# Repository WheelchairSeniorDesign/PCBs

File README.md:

# PCB Design in Git

- We will be using git to store KiCad files as well so that we can have a running record of them.
- Put all the PCBs in a subfolder in the PCB repo.
- Make a branch for your board, and only work on that board on the corresponding branch.
- Don’t delete your branch once you merge it; keep making changes on that branch.
- Only one person should work on a board at a time, and all changes should be committed before the next person works on it.

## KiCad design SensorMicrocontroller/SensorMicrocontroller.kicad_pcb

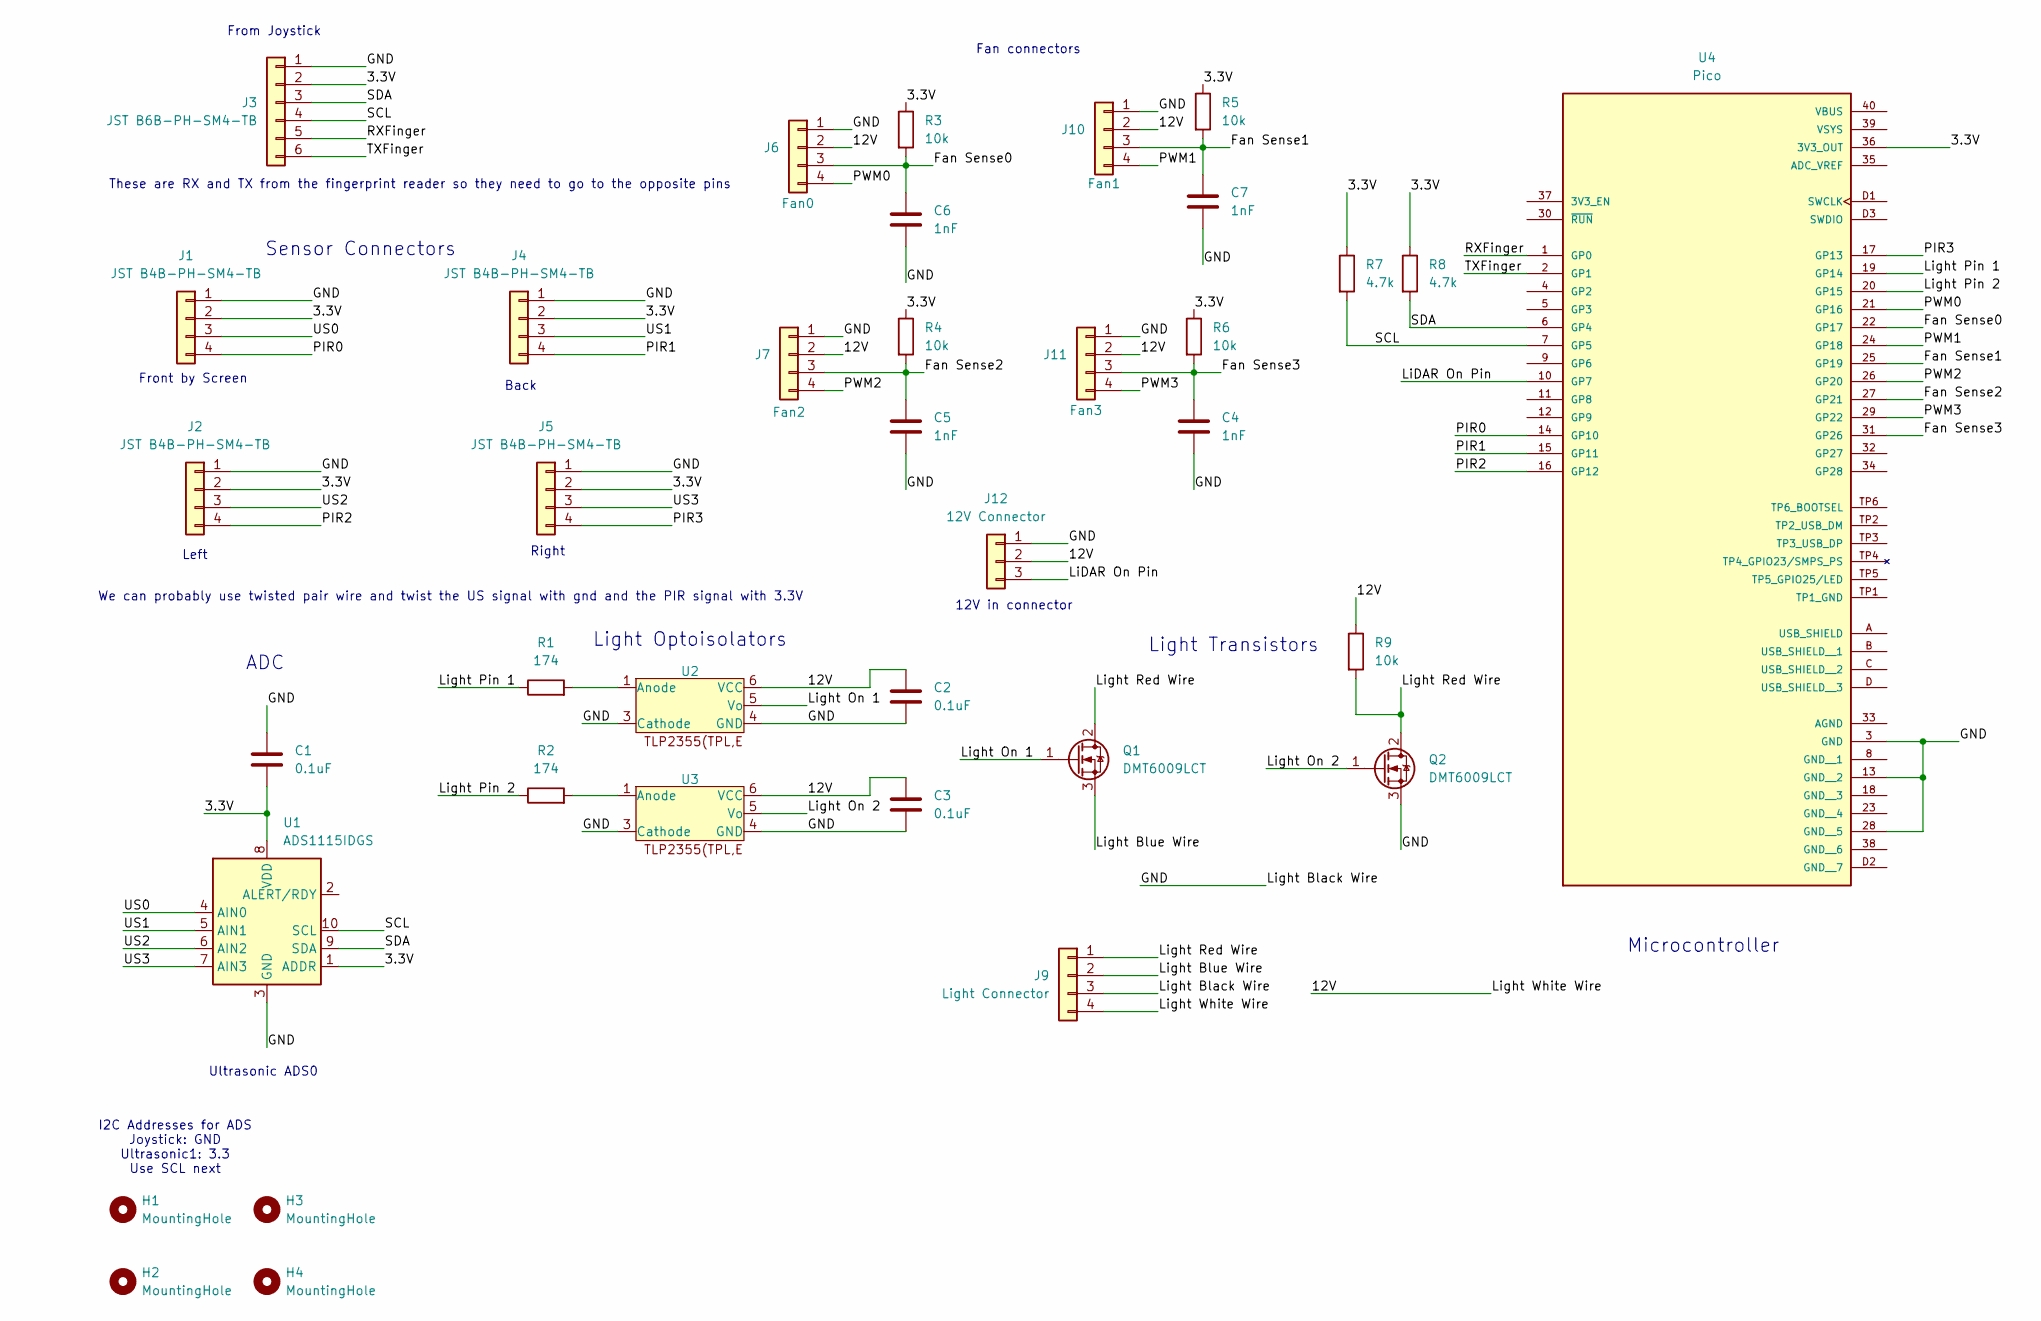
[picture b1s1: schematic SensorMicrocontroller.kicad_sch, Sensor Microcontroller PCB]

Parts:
C1, C2, C3: 0.1uF; C_0805_2012Metric; Manufacturer Part Number CC0805KRX7R9BB104
C4, C5, C6, C7: 1nF; C_0805_2012Metric; Manufacturer Part Number C0805C102K4RACTU
H1, H2, H3, H4: MountingHole; MountingHole_3.2mm_M3_ISO7380_Pad
J1, J2, J4, J5: JST B4B-PH-SM4-TB; JST_PH_B4B-PH-SM4-TB_1x04-1MP_P2.00mm_Vertical; Manufacturer Part Number B4B-PH-SM4-TB
J3: JST B6B-PH-SM4-TB; JST_PH_B6B-PH-SM4-TB_1x06-1MP_P2.00mm_Vertical; Manufacturer Part Number B6B-PH-SM4-TB
J6, J7, J10, J11: FanPinHeader_1x04_P2.54mm_Vertical; Manufacturer Part Number 0470531000
J9: Light Connector; JST_EH_B4B-EH-A_1x04_P2.50mm_Vertical; Manufacturer Part Number B4B-EH-A
J12: 12V Connector; JST_PH_B3B-PH-SM4-TB_1x03-1MP_P2.00mm_Vertical; Manufacturer Part Number B3B-PH-SM4-TB
Q1, Q2: DMT6009LCT; TO-220-3_Vertical; Manufacturer Part Number DMT6009LCT
R1, R2: 174; R_0805_2012Metric; Manufacturer Part Number RC0805FR-07174RL
R3, R4, R5, R6, R9: 10k; R_0805_2012Metric; Manufacturer Part Number RR1220P-103-D
R7, R8: 4.7k; R_0805_2012Metric; Manufacturer Part Number CRCW08054K70FKEAC
U1: ADS1115IDGS; VSSOP-10_3x3mm_P0.5mm; Manufacturer Part Number ADS1115IDGSR
U2, U3: Optoisolators; SO-5-6_4.55x3.7mm_P1.27mm; Manufacturer Part Number TLP2355(TPL,E
U4: Pico; pico; PARTREV 1.9

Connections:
/3.3V: C1.2, J1.2, J2.2, J3.2, J4.2, J5.2, R3.1, R4.1, R5.1, R6.1, R7.1, R8.1, U1.1 (ADDR), U1.8 (VDD), U4.36 (3V3_OUT)
/12V: C2.1, C3.1, J6.2, J7.2, J9.4, J10.2, J11.2, J12.2, R9.1, U2.6 (VCC), U3.6 (VCC)
/Fan Sense0: C6.1, J6.3, R3.2, U4.22 (GP17)
/Fan Sense1: C7.1, J10.3, R5.2, U4.25 (GP19)
/Fan Sense2: C5.1, J7.3, R4.2, U4.27 (GP21)
/Fan Sense3: C4.1, J11.3, R6.2, U4.31 (GP26)
/GND: C1.1, C2.2, C3.2, C4.2, C5.2, C6.2, C7.2, J1.1, J2.1, J3.1, J4.1, J5.1, J6.1, J7.1, J9.3, J10.1, J11.1, J12.1, Q2.3 (S), U1.3 (GND), U2.3 (Cathode), U2.4 (GND), U3.3 (Cathode), U3.4 (GND), U4.3 (GND), U4.13 (GND__2), U4.28 (GND__5)
/LiDAR On Pin: J12.3, U4.10 (GP7)
/Light Blue Wire: J9.2, Q1.3 (S)
/Light On 1: Q1.1 (G), U2.5 (Vo)
/Light On 2: Q2.1 (G), U3.5 (Vo)
/Light Pin 1: R1.1, U4.19 (GP14)
/Light Pin 2: R2.1, U4.20 (GP15)
/Light Red Wire: J9.1, Q1.2 (D), Q2.2 (D), R9.2
/PIR0: J1.4, U4.14 (GP10)
/PIR1: J4.4, U4.15 (GP11)
/PIR2: J2.4, U4.16 (GP12)
/PIR3: J5.4, U4.17 (GP13)
/PWM0: J6.4, U4.21 (GP16)
/PWM1: J10.4, U4.24 (GP18)
/PWM2: J7.4, U4.26 (GP20)
/PWM3: J11.4, U4.29 (GP22)
/RXFinger: J3.5, U4.1 (GP0)
/SCL: J3.4, R7.2, U1.10 (SCL), U4.7 (GP5)
/SDA: J3.3, R8.2, U1.9 (SDA), U4.6 (GP4)
/TXFinger: J3.6, U4.2 (GP1)
/US0: J1.3, U1.4 (AIN0)
/US1: J4.3, U1.5 (AIN1)
/US2: J2.3, U1.6 (AIN2)
/US3: J5.3, U1.7 (AIN3)
unnamed: R1.2, U2.1 (Anode)
unnamed: R2.2, U3.1 (Anode)

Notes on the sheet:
Microcontroller
Right
ADC
Light Transistors
Back
Sensor Connectors
Left
These are RX and TX from the fingerprint reader so they need to go to the opposite pins
From Joystick
Front by Screen
Fan connectors
Light Optoisolators
Ultrasonic ADS0
I2C Addresses for ADS Joystick: GND Ultrasonic1: 3.3 Use SCL next
12V in connector
We can probably use twisted pair wire and twist the US signal with gnd and the PIR signal with 3.3V

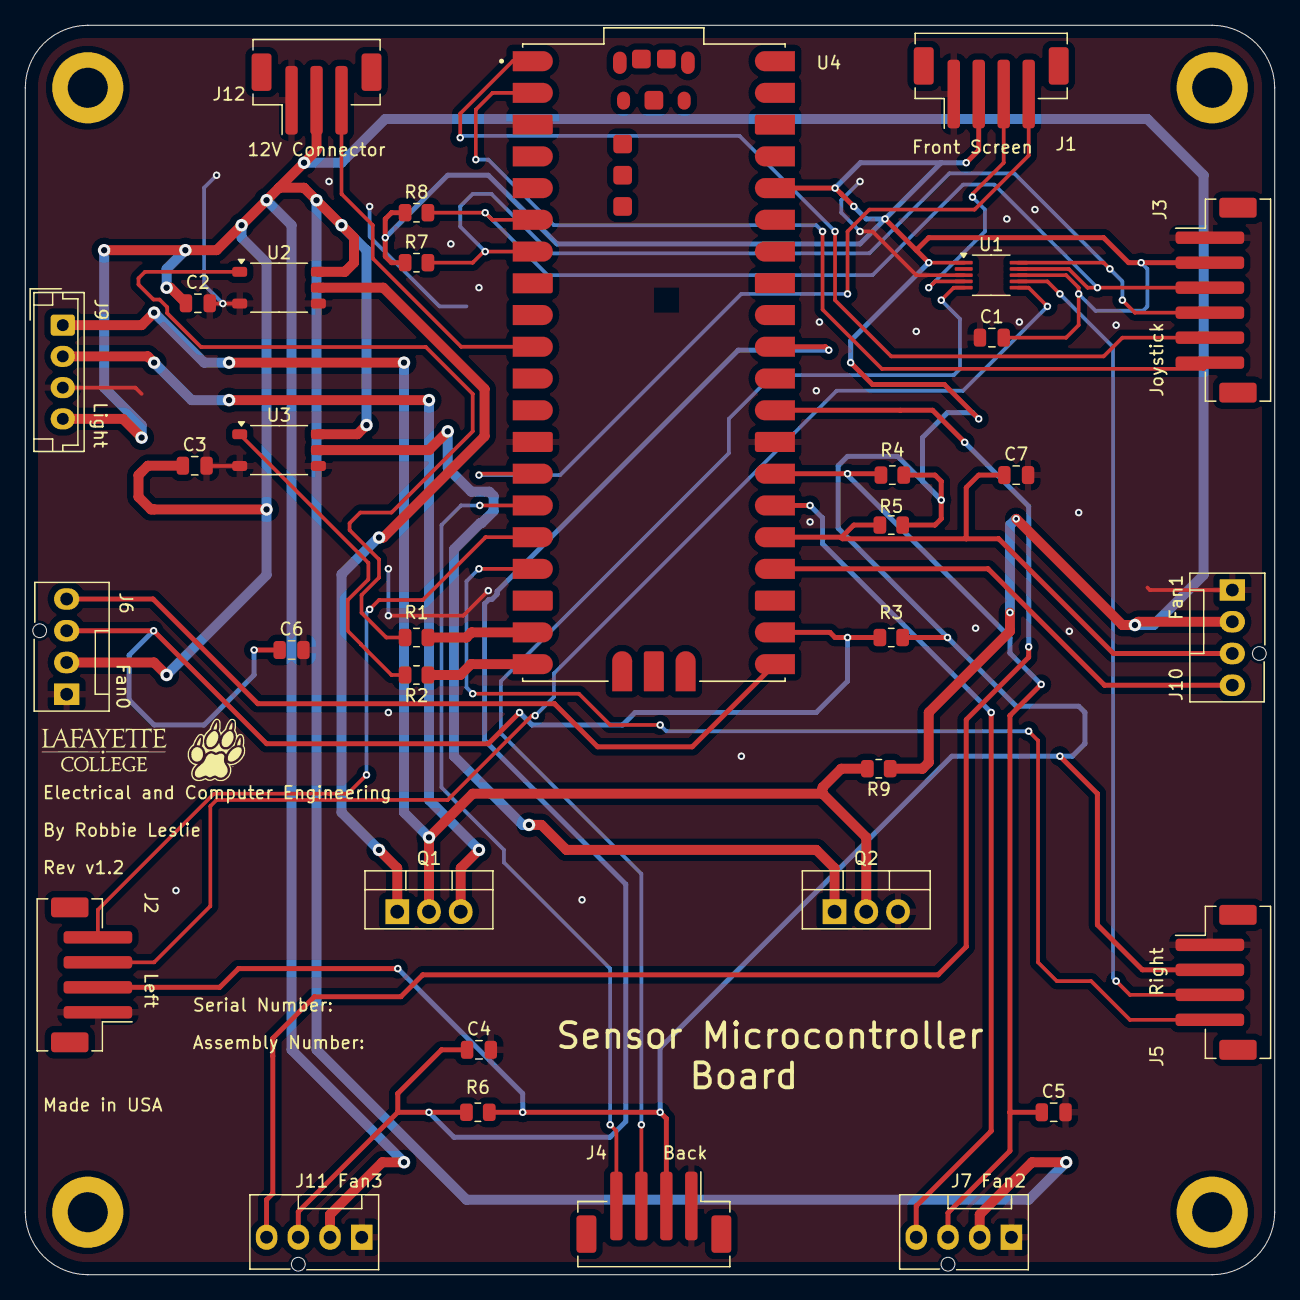
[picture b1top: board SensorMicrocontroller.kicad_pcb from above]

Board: 2 copper layers, 100.0 x 100.0 mm, 37 parts (0 on the bottom side), 32 nets.

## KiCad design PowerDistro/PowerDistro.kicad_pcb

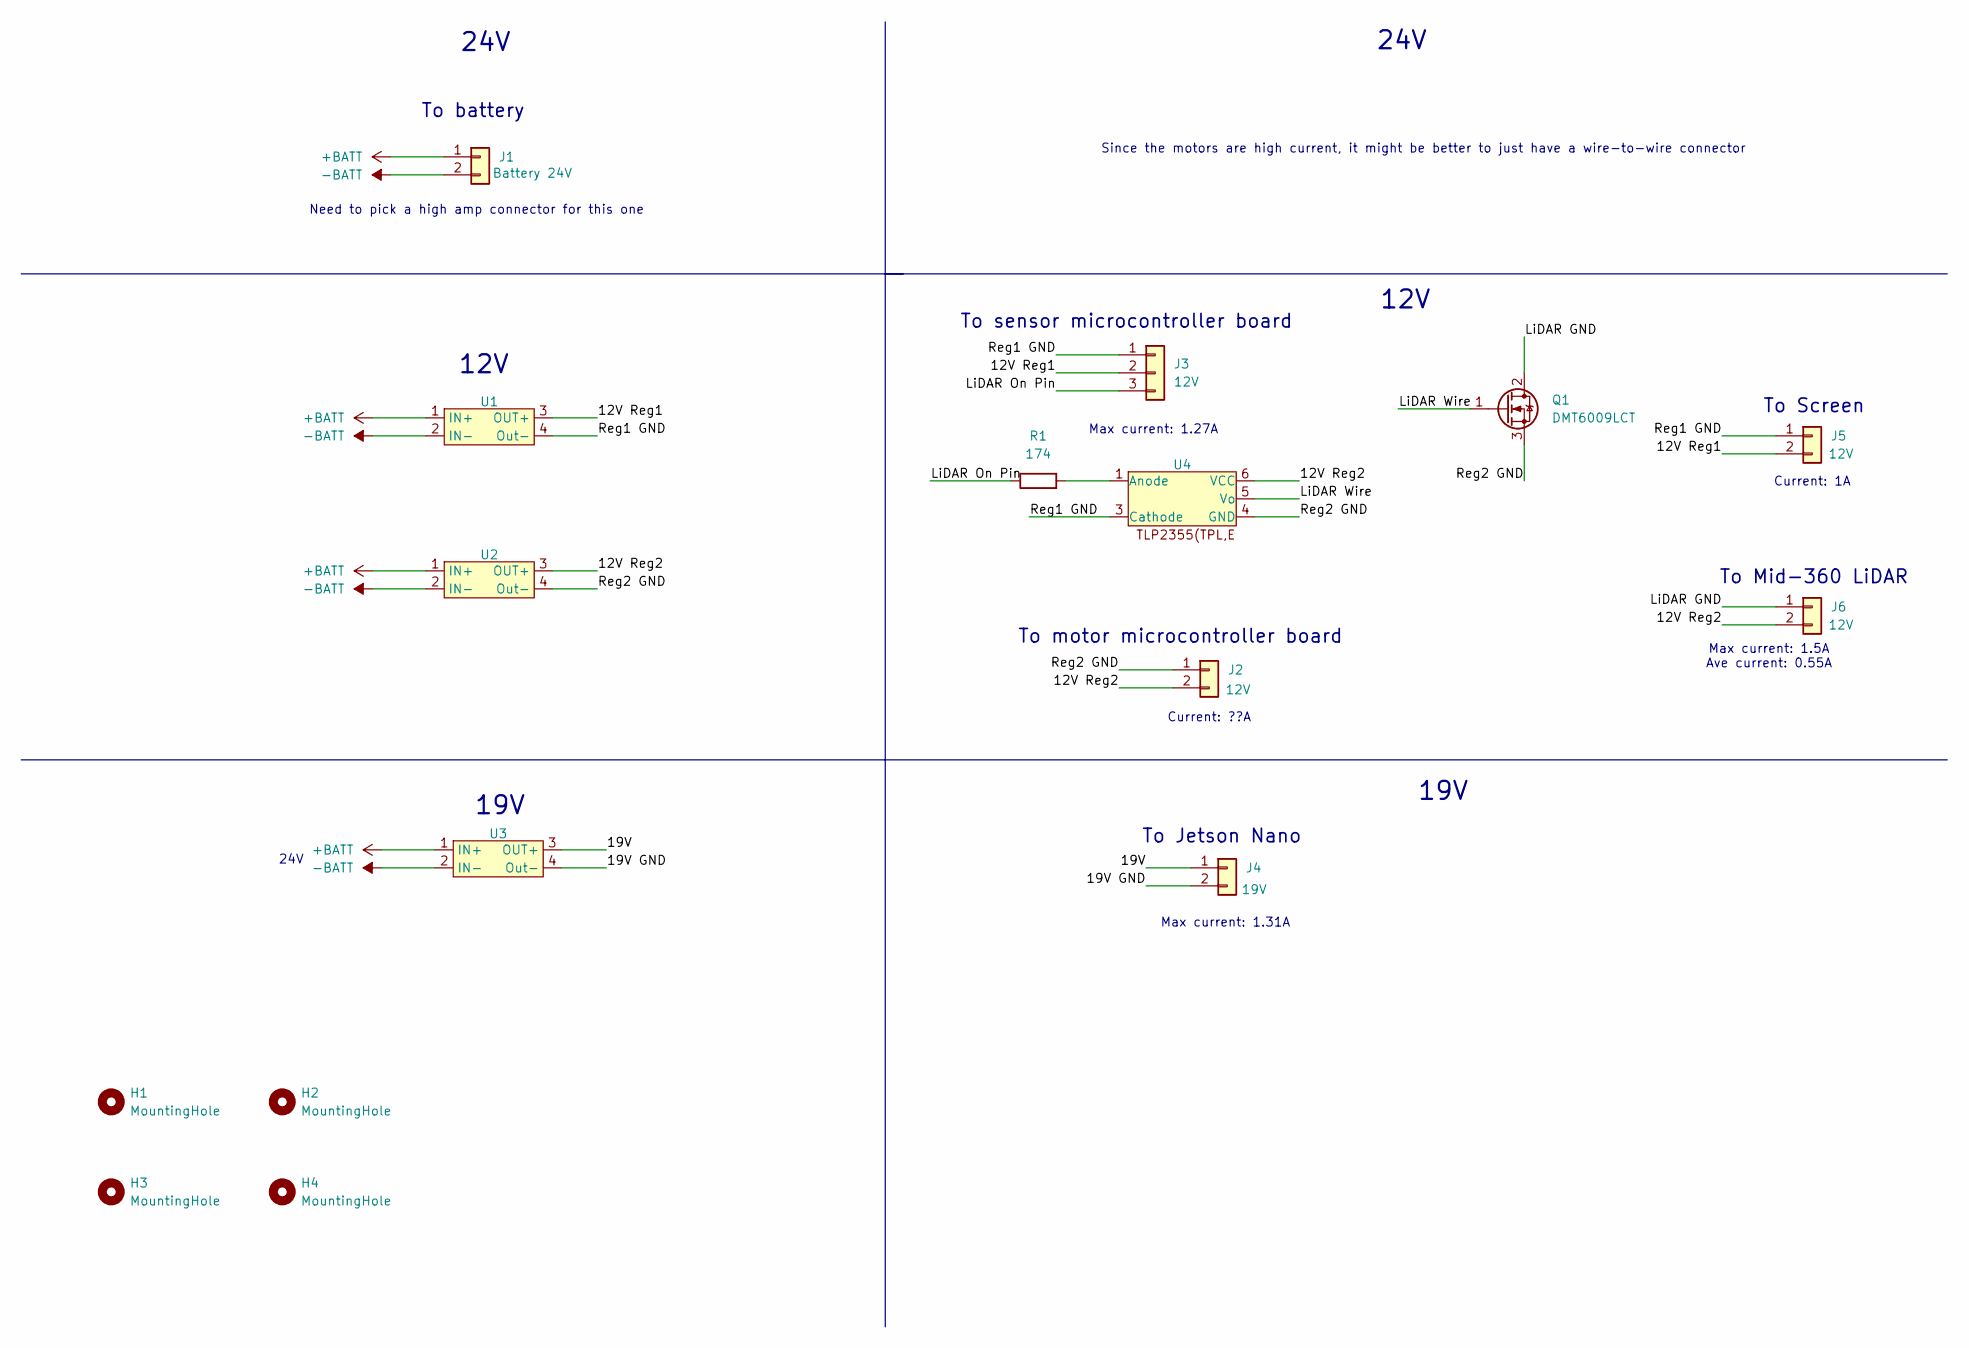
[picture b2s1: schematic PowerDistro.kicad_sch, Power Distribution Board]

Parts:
H1, H2, H3, H4: MountingHole; MountingHole_3.2mm_M3_ISO7380_Pad
J1: Molex_Mini-Fit_Jr_5566-02A_2x01_P4.20mm_Vertical; Manufacturer Part Number 0039290023
J2: JST_PH_S2B-PH-SM4-TB_1x02-1MP_P2.00mm_Horizontal; Manufacturer Part Number S2B-PH-SM4-TB
J3: 12V; JST_PH_S3B-PH-SM4-TB_1x03-1MP_P2.00mm_Horizontal; Manufacturer Part Number S3B-PH-SM4-TB
J4, J5, J6: JST_XH_S2B-XH-A-1_1x02_P2.50mm_Horizontal; Manufacturer Part Number S2B-XH-A-1
Q1: DMT6009LCT; TO-220-3_Vertical; Manufacturer Part Number DMT6009LCT
R1: 174; R_0805_2012Metric; Manufacturer Part Number RC0805FR-07174RL
U1, U2, U3: LM2596
U4: Optoisolators; SO-5-6_4.55x3.7mm_P1.27mm; Manufacturer Part Number TLP2355(TPL,E

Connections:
+BATT: J1.1, U1.1 (IN+), U2.1 (IN+), U3.1 (IN+)
-BATT: J1.2, U1.2 (IN-), U2.2 (IN-), U3.2 (IN-)
/12V Reg1: J3.2, J5.2, U1.3 (OUT+)
/12V Reg2: J2.2, J6.2, U2.3 (OUT+), U4.6 (VCC)
/19V: J4.1, U3.3 (OUT+)
/19V GND: J4.2, U3.4 (Out-)
/LiDAR GND: J6.1, Q1.2 (D)
/LiDAR On Pin: J3.3, R1.1
/LiDAR Wire: Q1.1 (G), U4.5 (Vo)
/Reg1 GND: J3.1, J5.1, U1.4 (Out-), U4.3 (Cathode)
/Reg2 GND: J2.1, Q1.3 (S), U2.4 (Out-), U4.4 (GND)
unnamed: R1.2, U4.1 (Anode)

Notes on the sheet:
Current: 1A
24V
To Jetson Nano
To battery
19V
12V
Max current: 1.27A
Since the motors are high current, it might be better to just have a wire-to-wire connector
To sensor microcontroller board
To motor microcontroller board
To Mid-360 LiDAR
Need to pick a high amp connector for this one
To Screen
Current: ??A
Max current: 1.5A Ave current: 0.55A
Max current: 1.31A

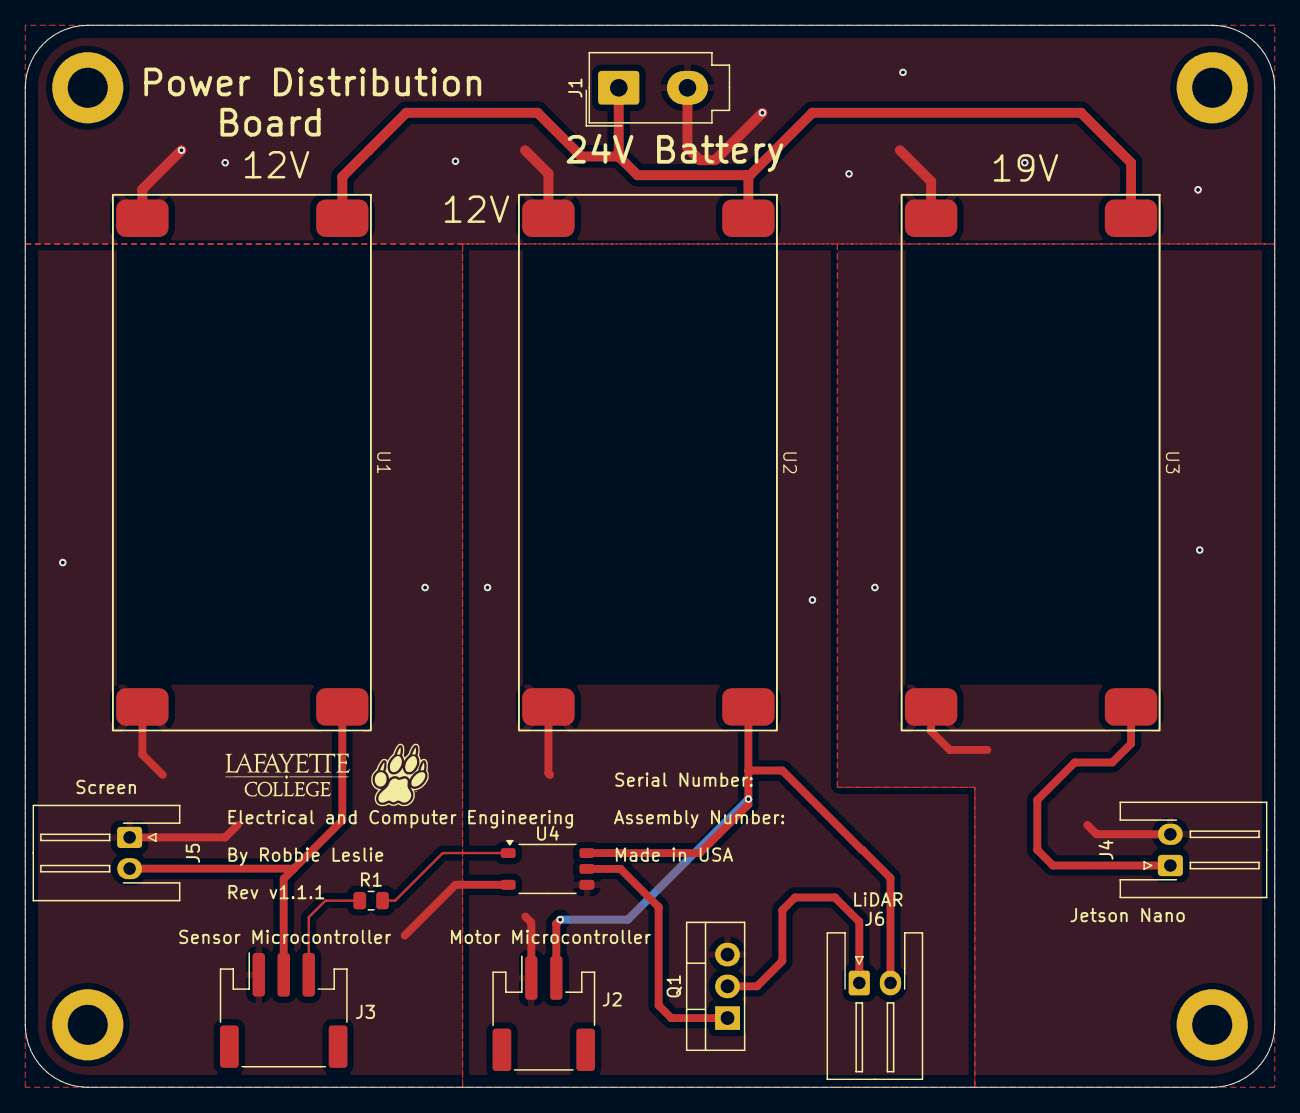
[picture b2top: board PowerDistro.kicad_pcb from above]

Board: 2 copper layers, 100.0 x 85.0 mm, 16 parts (0 on the bottom side), 12 nets.

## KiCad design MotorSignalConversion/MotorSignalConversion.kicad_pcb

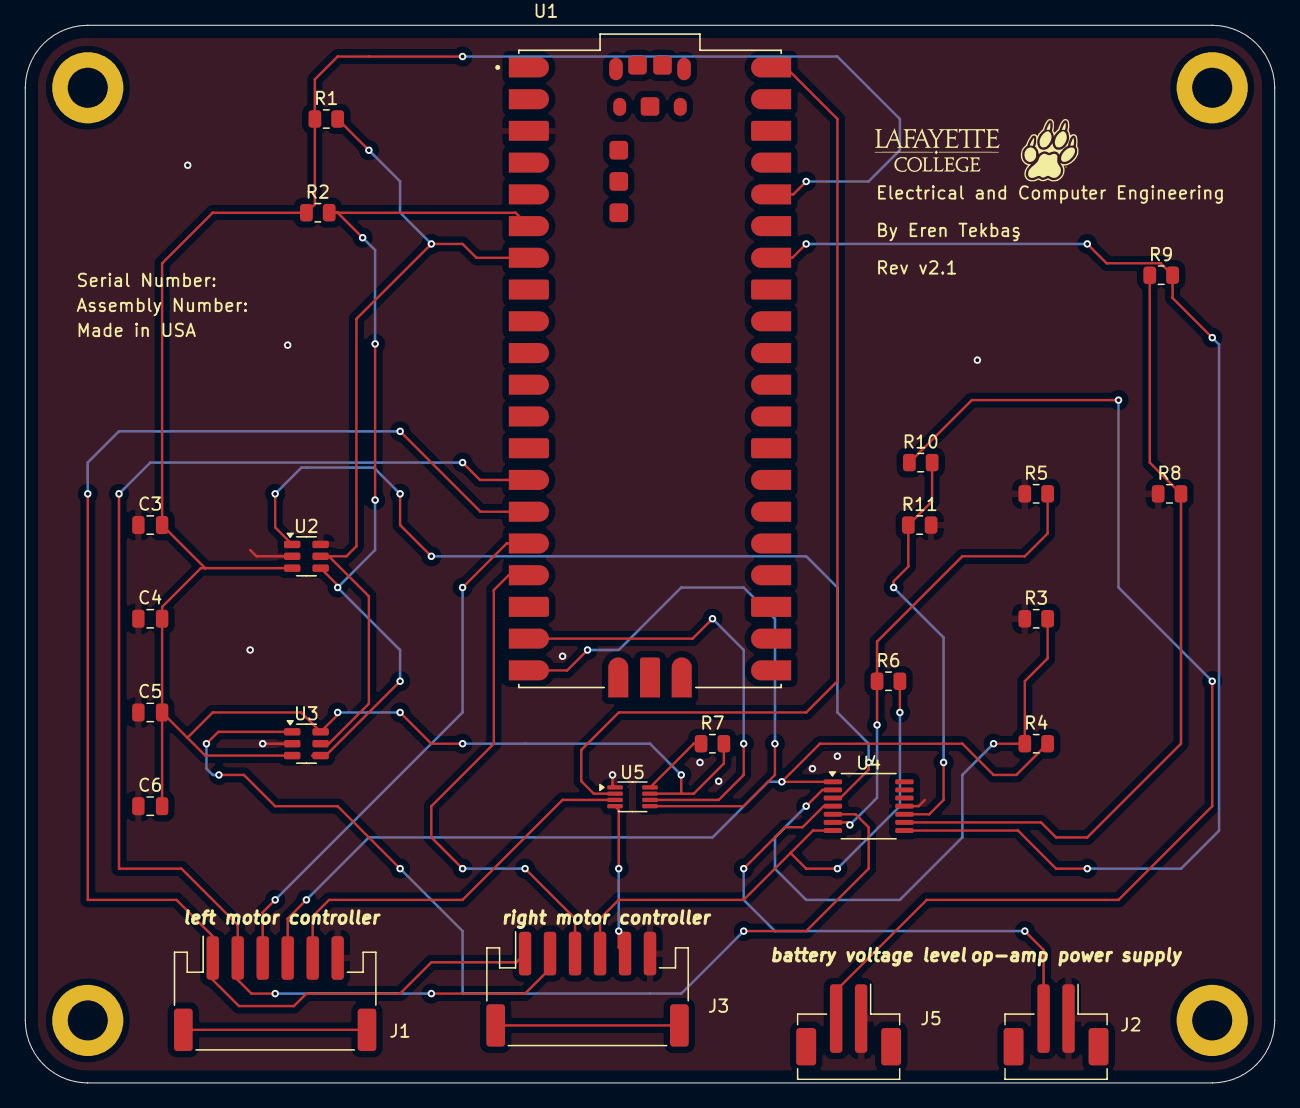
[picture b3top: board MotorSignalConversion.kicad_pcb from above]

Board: 2 copper layers, 100.0 x 84.7 mm, 28 parts (0 on the bottom side), 25 nets.

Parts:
C3, C5: 10 uF; C_0805_2012Metric
C4, C6: 0.1 uF; C_0805_2012Metric
H1, H2, H3, H4: MountingHole; MountingHole_3.2mm_M3_ISO7380_Pad
J1, J3: Conn_01x06_MountingPin; JST_PH_S6B-PH-SM4-TB_1x06-1MP_P2.00mm_Horizontal
J2, J5: Conn_01x02; JST_PH_B2B-PH-SM4-TB_1x02-1MP_P2.00mm_Vertical
R1, R2: 4.7K; R_0805_2012Metric
R3, R5: 900; R_0805_2012Metric
R4, R6: 2.1K; R_0805_2012Metric
R7: 200K; R_0805_2012Metric
R8, R11: 10K; R_0805_2012Metric
R9: 91K; R_0805_2012Metric
R10: 820K; R_0805_2012Metric
U1: SC0915; pico
U2, U3: MCP4725xxx-xCH; SOT-23-6
U4: LM324; TSSOP-14_4.4x5mm_P0.65mm
U5: LSF0102DCUR; VSSOP-8_2.3x2mm_P0.5mm

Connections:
/3V3_OUT: C3.2, C4.2, C5.2, C6.2, R1.1, R2.1, R7.2, U1.36 (3V3_OUT), U2.3 (VDD), U3.3 (VDD), U3.6 (A0), U5.7 (VREF_B)
/5V_OUT: U1.40 (VBUS), U5.2 (VREF_A)
/12V: J2.2, U4.4 (V+)
/BatteryLevelRegulated: R9.2, U1.34 (GP28), U4.8
/BatteryLevelUnregulated: J5.2, R10.1
/Brake: J1.2, J3.2, U1.14 (GP10)
/DirectionL: J1.3, U1.16 (GP12)
/DirectionR: J3.3, U1.17 (GP13)
/Enable: J1.1, J3.1, U1.15 (GP11)
/GND: C3.1, C4.1, C5.1, C6.1, J1.6, J2.1, J3.6, J5.1, R3.1, R5.1, R8.1, R11.2, U1.3 (GND), U2.2 (VSS), U2.6 (A0), U3.2 (VSS), U4.11 (V-), U5.1 (GND)
/I2C SCL: R1.2, U1.7 (GP5), U2.5 (SCL), U3.5 (SCL)
/I2C SDA: R2.2, U1.6 (GP4), U2.4 (SDA), U3.4 (SDA)
/SpeedLeft: J1.4, R4.2, U4.1
/SpeedReadRegulatedL: U1.19 (GP14), U5.6 (B1)
/SpeedReadRegulatedR: U1.20 (GP15), U5.5 (B2)
/SpeedReadUL: J1.5, U5.3 (A1)
/SpeedReadUR: J3.5, U5.4 (A2)
/SpeedRight: J3.4, R6.2, U4.7
/VOUT1: U2.1 (VOUT), U4.3 (+)
/VOUT2: U3.1 (VOUT), U4.5 (+)
unnamed: R3.2, R4.1, U4.2 (-)
unnamed: R5.2, R6.1, U4.6 (-)
unnamed: R10.2, R11.1, U4.10 (+)
unnamed: R8.2, R9.1, U4.9 (-)
unnamed: R7.1, U5.8 (EN)

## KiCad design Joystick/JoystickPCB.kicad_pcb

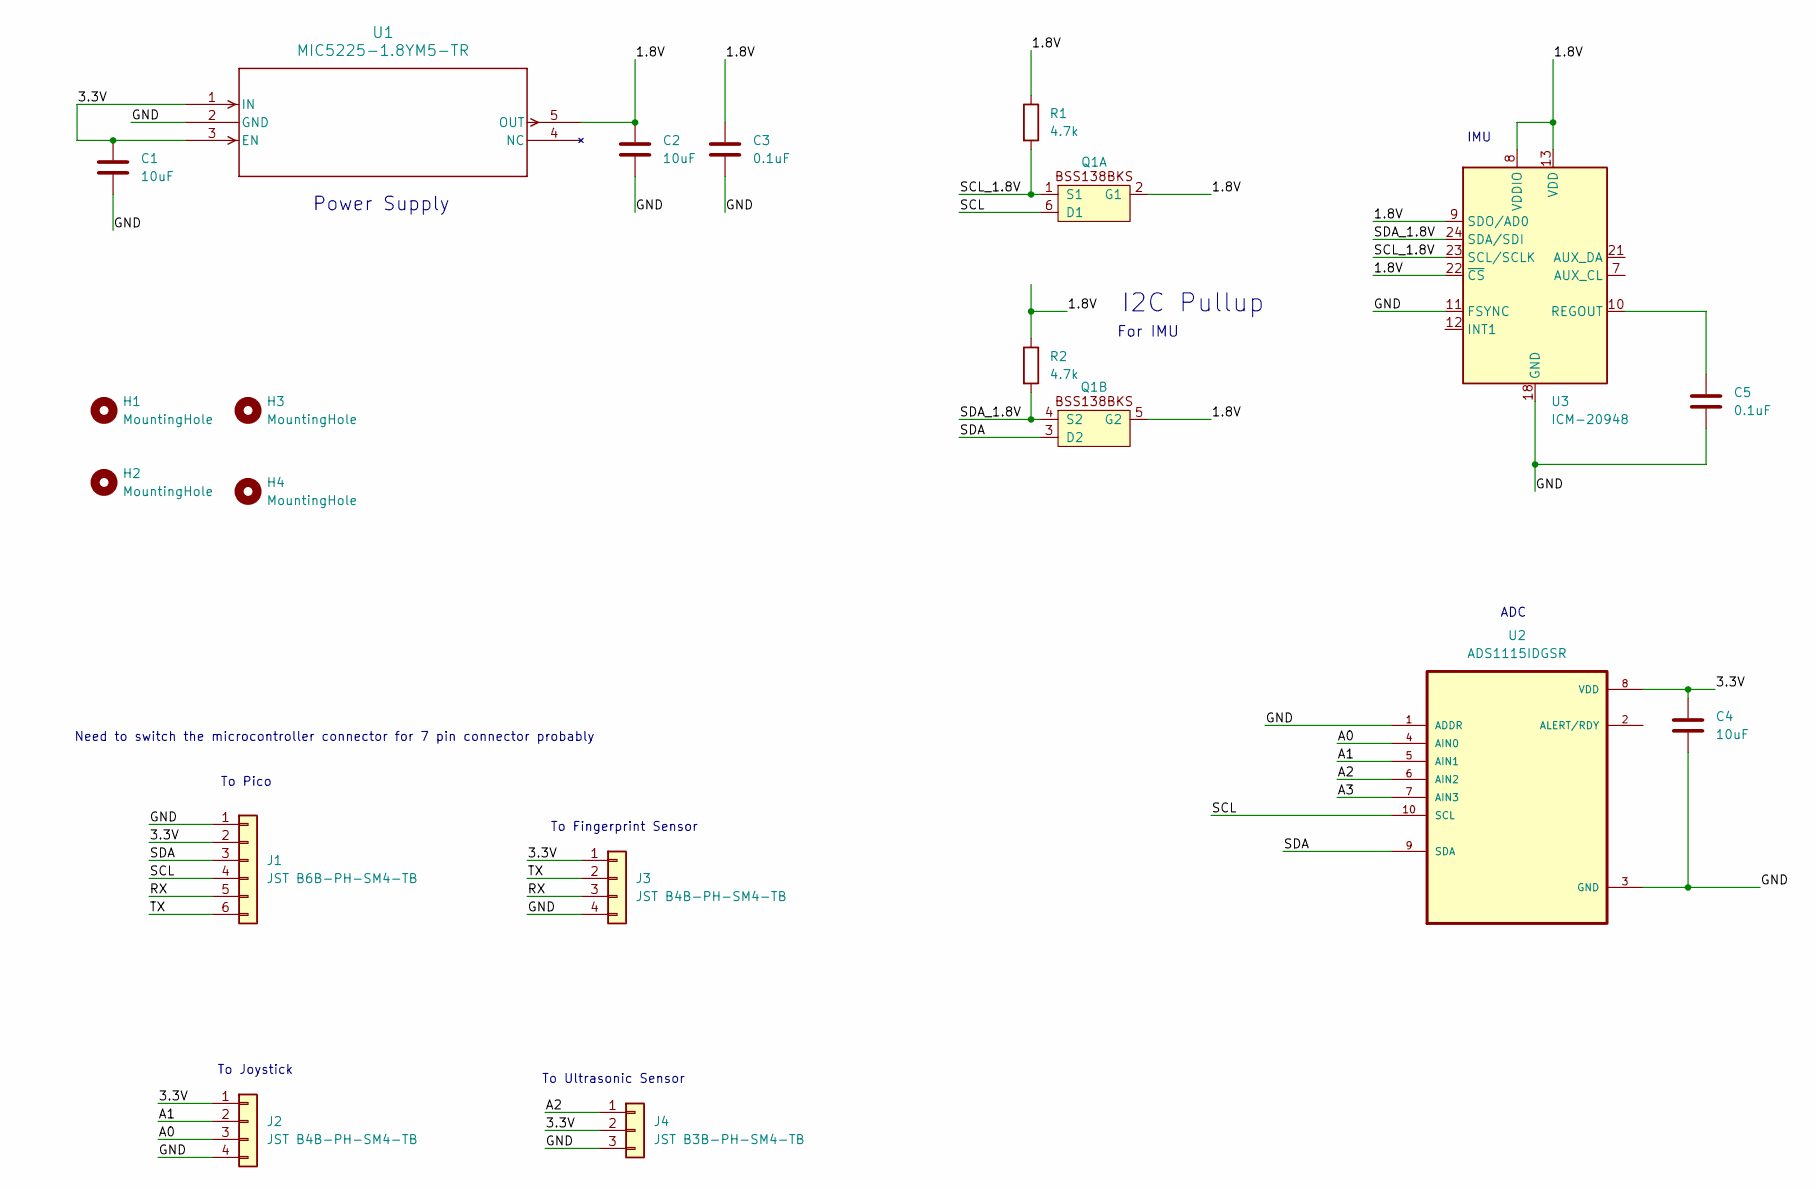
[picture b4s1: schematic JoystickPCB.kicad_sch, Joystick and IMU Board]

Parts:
C1, C2, C4: 10uF; C_0805_2012Metric; Manufacturer Part Number GRM21BR61C106KE15K
C3, C5: 0.1uF; C_0805_2012Metric; Manufacturer Part Number CC0805KRX7R9BB104
H1, H2, H3, H4: MountingHole; MountingHole_3.2mm_M3_ISO7380_Pad
J1: JST B6B-PH-SM4-TB; JST_PH_S6B-PH-SM4-TB_1x06-1MP_P2.00mm_Horizontal; Manufacturer Part Number S6B-PH-SM4-TB
J2, J3: JST B4B-PH-SM4-TB; JST_PH_B4B-PH-SM4-TB_1x04-1MP_P2.00mm_Vertical; Manufacturer Part Number B4B-PH-SM4-TB
J4: JST B3B-PH-SM4-TB; JST_PH_B3B-PH-SM4-TB_1x03-1MP_P2.00mm_Vertical; Manufacturer Part Number B3B-PH-SM4-TB
Q1: SOT-363_SC-70-6; Manufacturer Part Number BSS138BKS,115
R1, R2: 4.7k; R_0805_2012Metric; Manufacturer Part Number CRCW08054K70FKEAC
U1: MIC5225-1.8YM5-TR; SOT-23-5; Manufacturer Part Number MIC5225-1.8YM5-TR
U2: ADS1115IDGSR; VSSOP-10_3x3mm_P0.5mm; Manufacturer Part Number ADS1115IDGSR
U3: ICM-20948; InvenSense_QFN-24_3x3mm_P0.4mm; Manufacturer Part Number ICM-20948

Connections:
/1.8V: C2.1, C3.1, Q1.2 (G1), Q1.5 (G2), R1.1, R2.1, U1.5 (OUT), U3.8 (VDDIO), U3.9 (SDO/AD0), U3.13 (VDD), U3.22 (~CS)
/3.3V: C1.1, C4.1, J1.2, J2.1, J3.1, J4.2, U1.1 (IN), U1.3 (EN), U2.8 (VDD)
/A0: J2.3, U2.4 (AIN0)
/A1: J2.2, U2.5 (AIN1)
/A2: J4.1, U2.6 (AIN2)
/A3: U2.7 (AIN3)
/GND: C1.2, C2.2, C3.2, C4.2, C5.2, J1.1, J2.4, J3.4, J4.3, U1.2 (GND), U2.1 (ADDR), U2.3 (GND), U3.11 (FSYNC), U3.18 (GND), U3.20 (GND)
/RX: J1.5, J3.3
/SCL: J1.4, Q1.6 (D1), U2.10 (SCL)
/SCL_1.8V: Q1.1 (S1), R1.2, U3.23 (SCL/SCLK)
/SDA: J1.3, Q1.3 (D2), U2.9 (SDA)
/SDA_1.8V: Q1.4 (S2), R2.2, U3.24 (SDA/SDI)
/TX: J1.6, J3.2
unnamed: C5.1, U3.10 (REGOUT)

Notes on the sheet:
For IMU
Need to switch the microcontroller connector for 7 pin connector probably
To Fingerprint Sensor
IMU
To Joystick
I2C Pullup
To Pico
To Ultrasonic Sensor
Power Supply
ADC

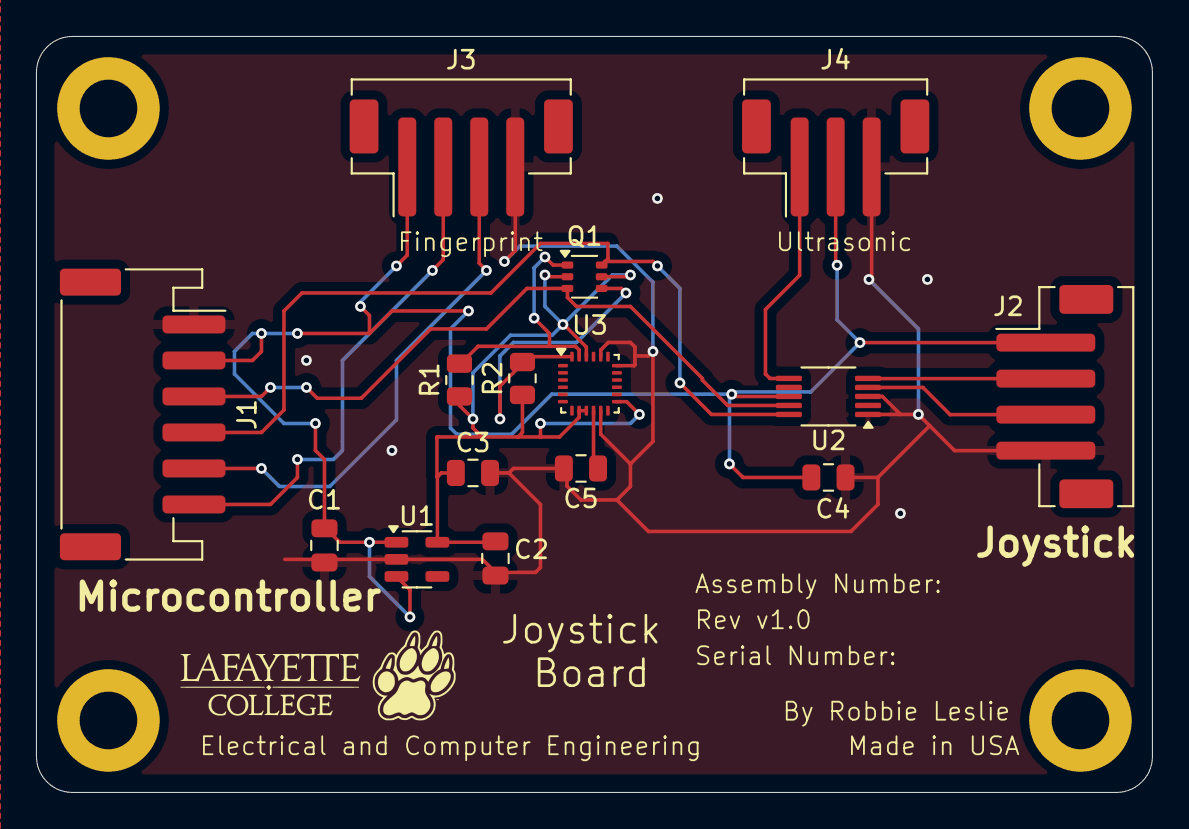
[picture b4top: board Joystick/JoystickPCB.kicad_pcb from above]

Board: 2 copper layers, 62.0 x 42.0 mm, 19 parts (0 on the bottom side), 13 nets.

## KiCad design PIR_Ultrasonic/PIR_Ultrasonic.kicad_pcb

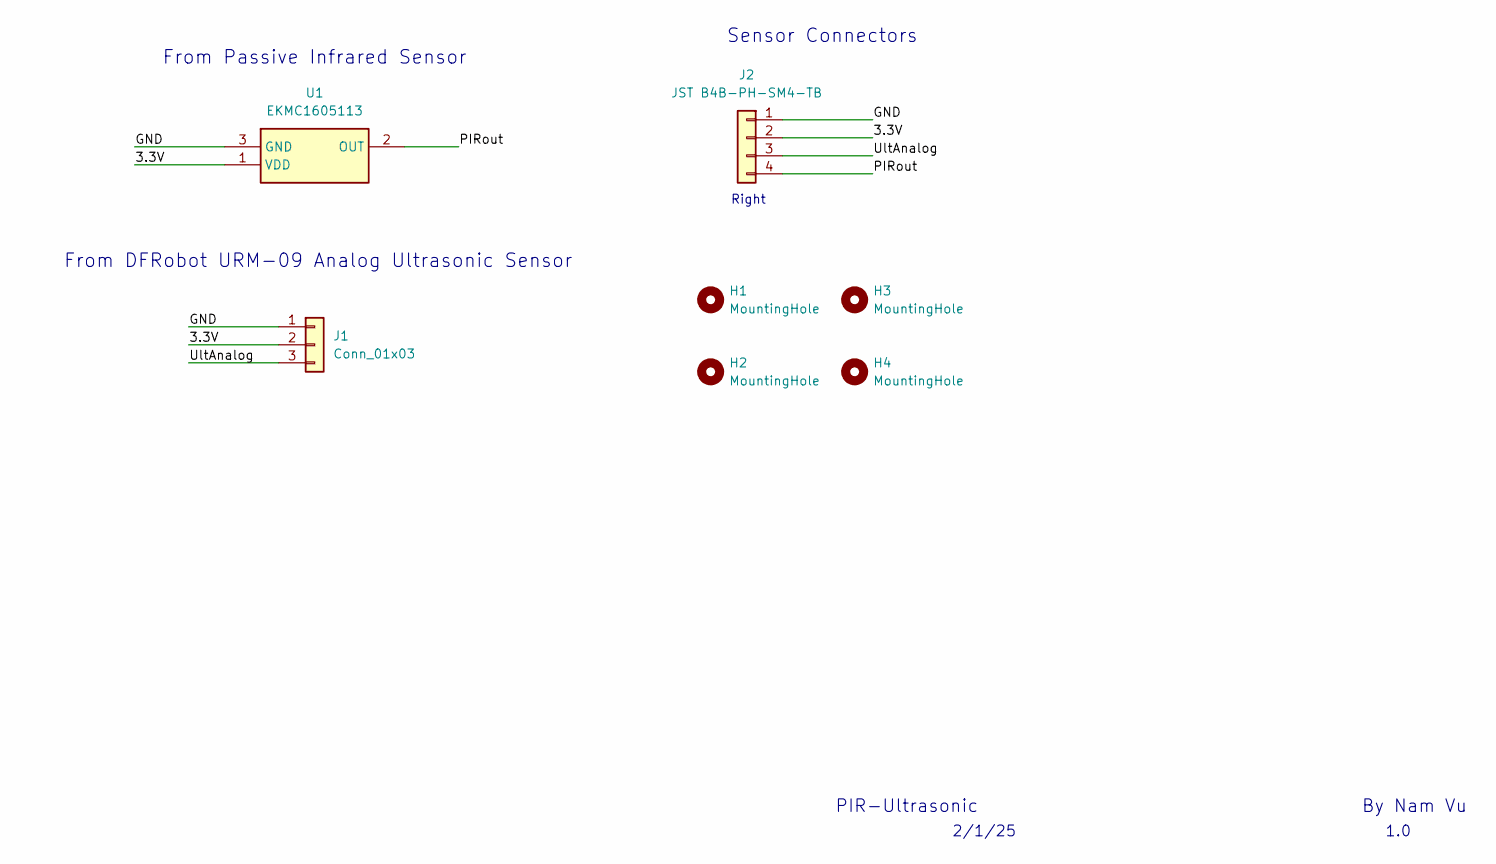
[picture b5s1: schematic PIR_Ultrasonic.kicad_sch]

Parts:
H1, H2, H3, H4: MountingHole; MountingHole_3.2mm_M3_ISO7380_Pad
J1: Conn_01x03; JST_PH_B3B-PH-SM4-TB_1x03-1MP_P2.00mm_Vertical; Manufacturer Part Number B3B-PH-SM4-TB
J2: JST B4B-PH-SM4-TB; JST_PH_B4B-PH-SM4-TB_1x04-1MP_P2.00mm_Vertical; Manufacturer Part Number B4B-PH-SM4-TB
U1: EKMC1605113; Mouser Part Number 667-EKMC1605113

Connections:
/3.3V: J1.2, J2.2, U1.1 (VDD)
/GND: J1.1, J2.1, U1.3 (GND)
/PIRout: J2.4, U1.2 (OUT)
/UltAnalog: J1.3, J2.3

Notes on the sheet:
From DFRobot URM-09 Analog Ultrasonic Sensor
Right
2/1/25
Sensor Connectors
From Passive Infrared Sensor
1.0
PIR-Ultrasonic
By Nam Vu

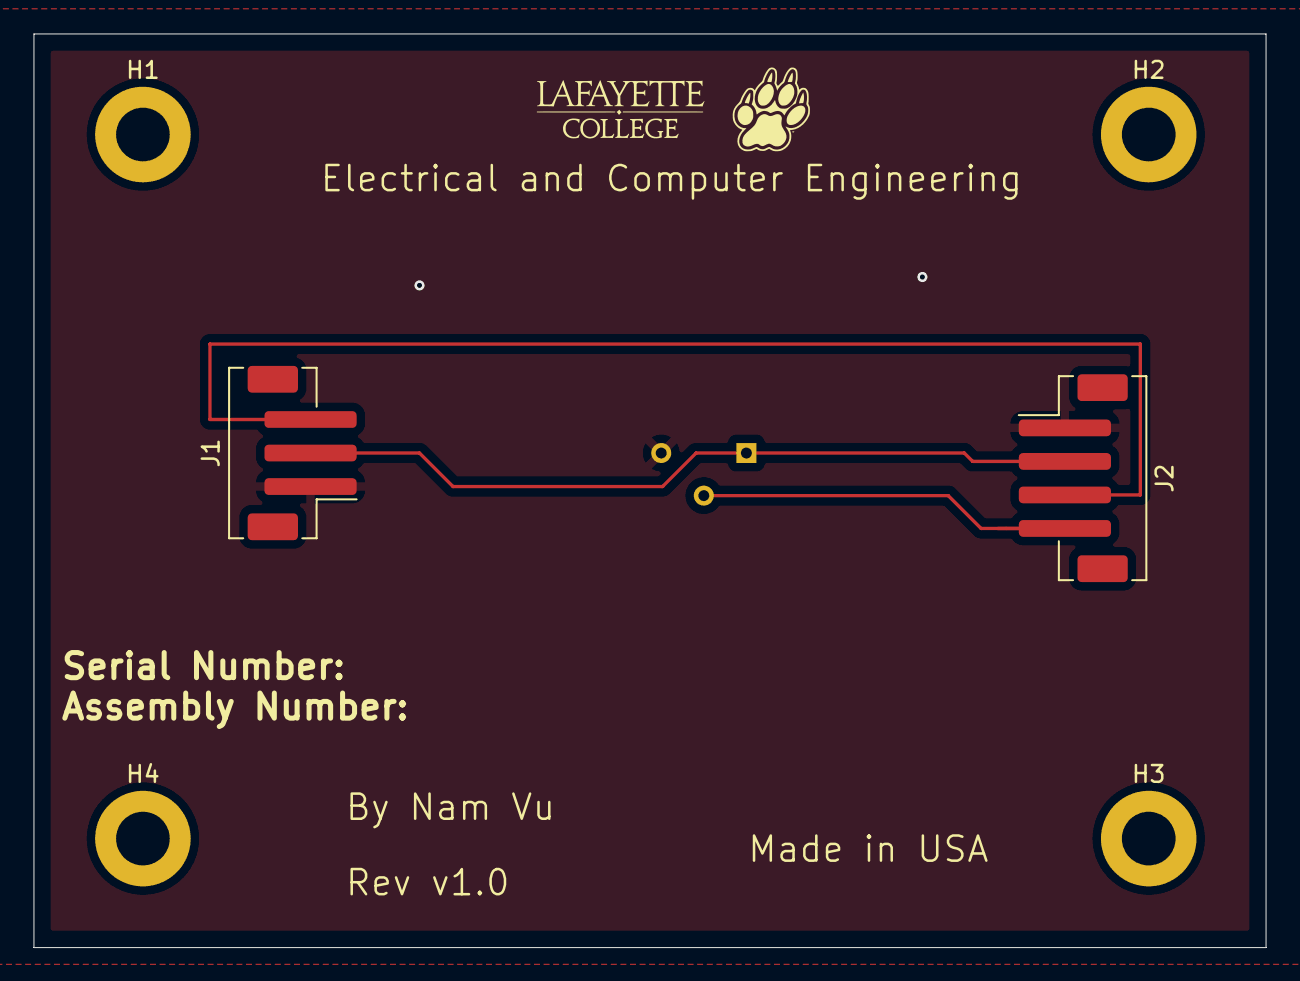
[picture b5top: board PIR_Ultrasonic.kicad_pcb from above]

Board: 2 copper layers, 73.5 x 54.5 mm, 7 parts (1 on the bottom side), 4 nets.
